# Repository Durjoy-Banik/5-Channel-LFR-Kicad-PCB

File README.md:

# 5-Channel Line Follower Robot (LFR) - Custom PCB Design

An end-to-end Robotics and Hardware Engineering project featuring a custom chassis-shaped PCB, optimized signal routing, and manufacturing-ready deliverables.

---

## 📌 Project Overview
The goal of this project was to design a professional, error-free, custom chassis-shaped 5-channel Line Follower Robot (LFR) PCB using KiCad (v9.0). It integrates power management, sensor interfacing, and motor driving capabilities directly onto a single board layout.

---

## 🛠️ Core Technical Highlights

### 1. Hardware & Component Integration
* **Microcontroller:** Arduino Uno (Shield-compatible design)
* **Sensors:** HW-871 5-Channel IR Sensor Array with dedicated pin headers
* **Actuation & Power:** L298N Motor Driver integration for dual-DC motor control

### 2. PCB Design & Signal Integrity (KiCad v9.0)
* **Custom Form Factor:** Custom chassis-shaped PCB outline engineered for mechanical stability and sleek aesthetics.
* **Routing Geometry:** Clean, professional 45-degree trace routing on Front Copper layer (F.Cu).
* **Trace Width:** Strict **0.4mm trace width** maintained for optimal current capacity and signal reliability.
* **Industrial Validation:** Achieved **0 Design Rule Check (DRC) errors and 0 warnings**.

### 3. Fabrication & Manufacturing Deliverables
* Fully generated production-ready fabrication files including:
  * **Gerber Files** (F.Cu, B.Cu, Mask, Silk, Edge.Cuts)
  * **NC Drill Files** (.drl)
  * **ZIP Archive** ready for direct submission to PCB manufacturers (e.g., JLCPCB, PCBWay).

---

## 📂 Repository Structure

```text
├── Schematic/          # KiCad schematic files (.kicad_sch)
├── PCB_Layout/         # KiCad PCB layout files (.kicad_pcb)
├── Gerber_Files/       # Fabrication-ready Gerber and Drill files (.zip)
└── Assets/             # Circuit diagrams and project documentation media

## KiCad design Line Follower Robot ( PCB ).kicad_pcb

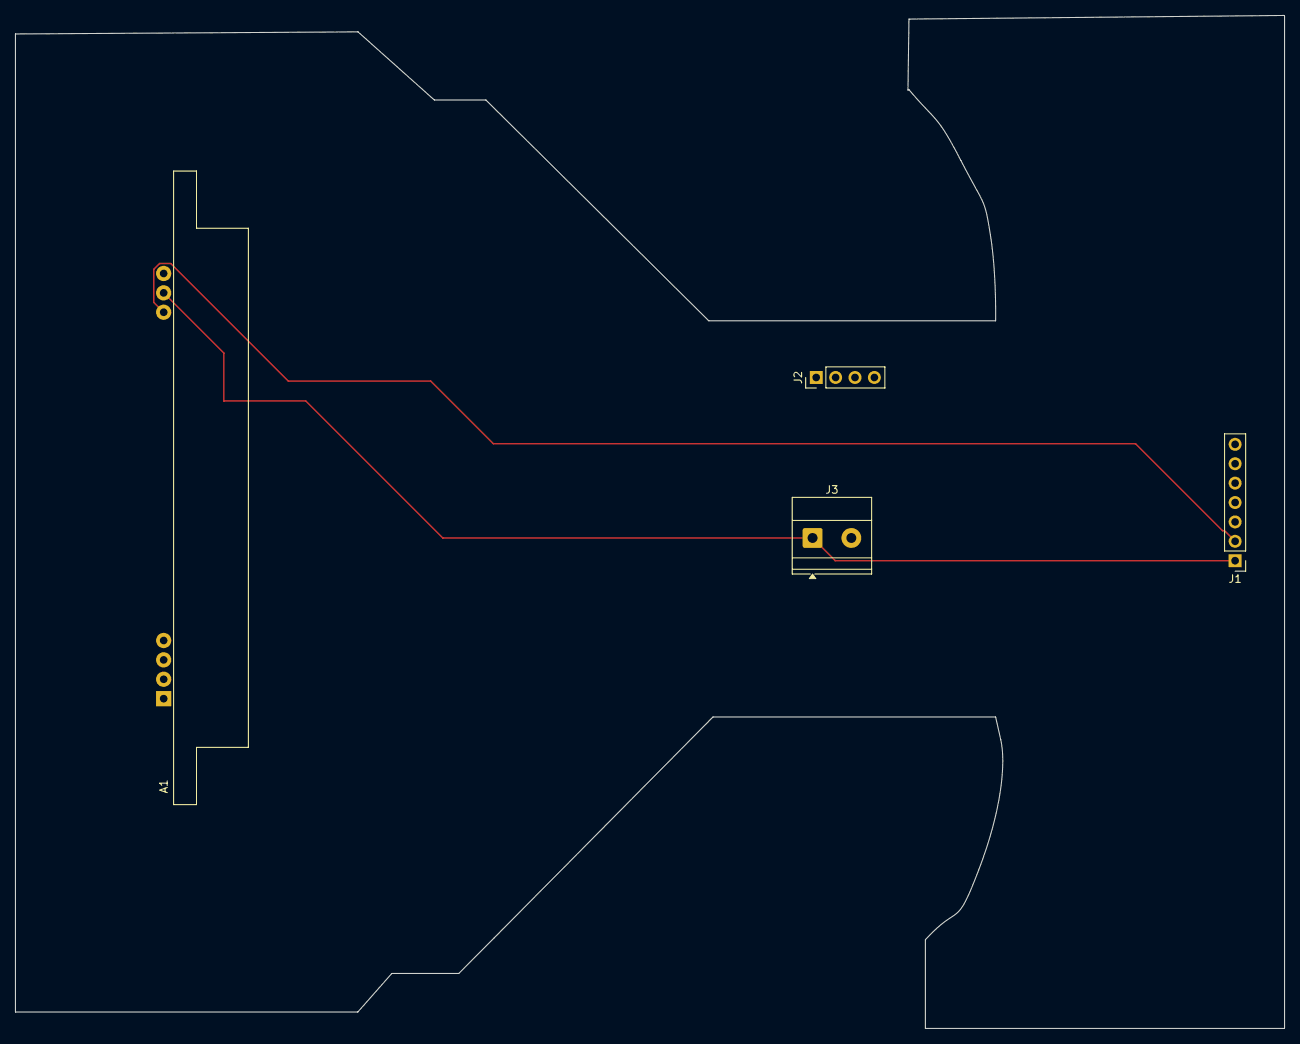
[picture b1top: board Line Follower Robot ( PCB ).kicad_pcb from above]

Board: 2 copper layers, 166.2 x 132.7 mm, 4 parts (0 on the bottom side), 2 nets.

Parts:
A1: Arduino_UNO_R2; Reverb_BTDR-1V
J1: Conn_01x07_Pin; PinHeader_1x07_P2.54mm_Vertical
J2: Conn_01x04_Pin; PinHeader_1x04_P2.54mm_Vertical
J3: Screw_Terminal_01x02; TerminalBlock_Phoenix_MKDS-1,5-2-5.08_1x02_P5.08mm_Horizont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

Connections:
/+5V: A1.5 (+5V), J1.2
/GND: A1.6 (GND), J1.1, J3.1
